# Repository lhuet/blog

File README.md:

Blog perso réalisé avec JBake -> http://lhuet.github.io/blog

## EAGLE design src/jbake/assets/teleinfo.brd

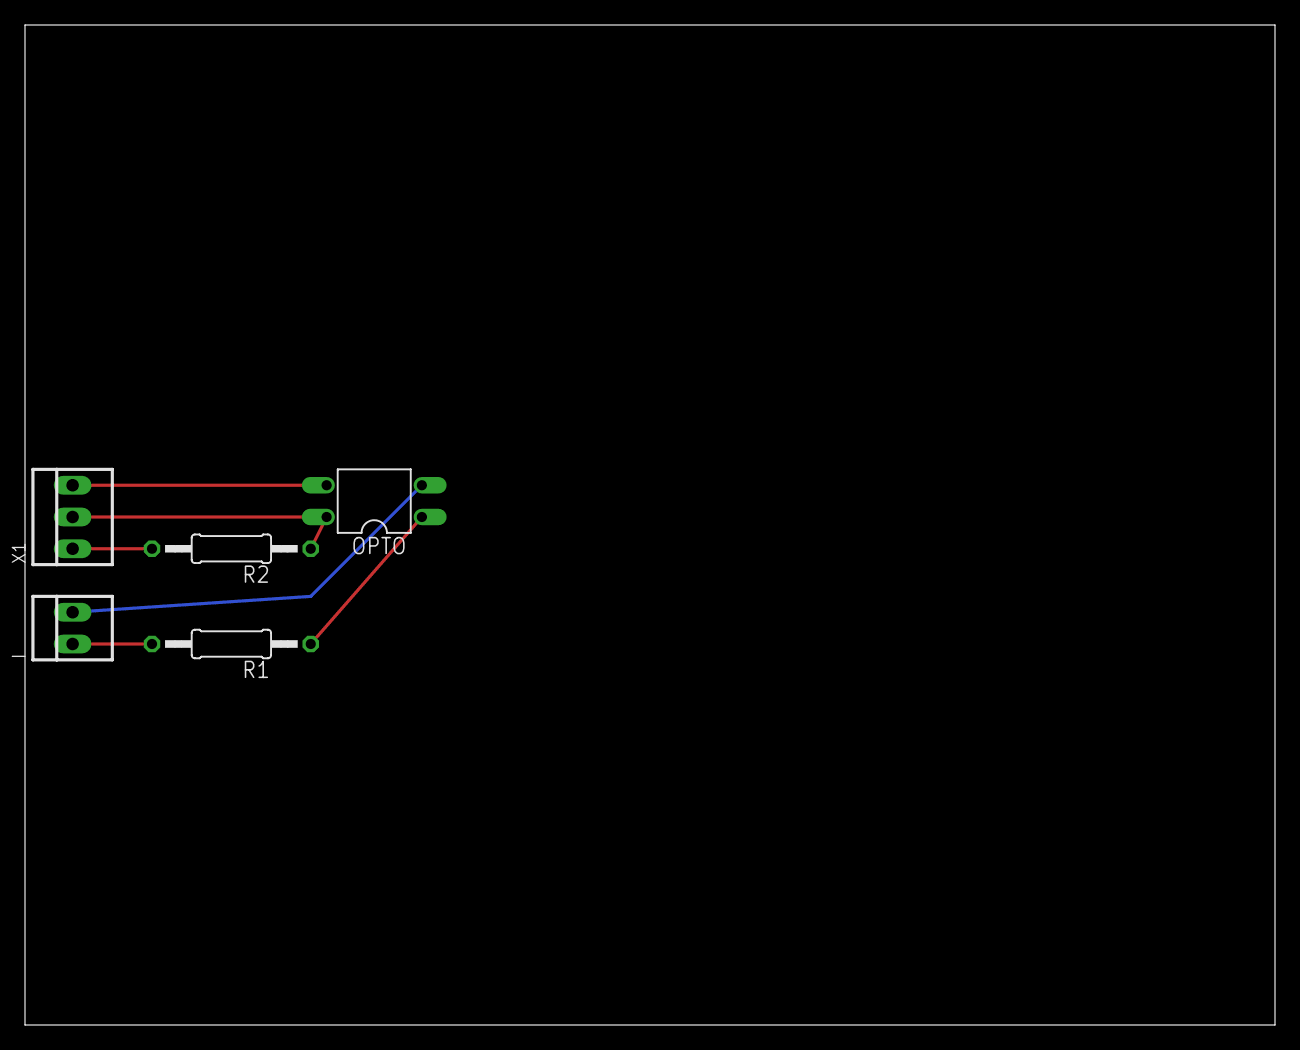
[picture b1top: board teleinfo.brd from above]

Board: 2 copper layers, 100.0 x 80.0 mm, 5 parts (0 on the bottom side), 6 nets.

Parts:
I: 22-23-2021
OPTO: SFH620A; DIL04
R1: 1.2k; 0207/12
R2: 3.3k; 0207/12
X1: 22-23-2031

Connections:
unnamed: OPTO.1, R1.1
unnamed: I.1, R1.2
unnamed: I.2, OPTO.2
unnamed: OPTO.4, R2.1, X1.2
unnamed: OPTO.3, X1.3
unnamed: R2.2, X1.1

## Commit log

2013-11-30 Premiere page de test
2013-12-01 init .gitignore
2013-12-01 init blog jbake
2013-12-01 ignore les fichiers générés
2013-12-01 migation template sous Bootstrap 3.0.2
2013-12-01 Template initial
2013-12-01 title change
2013-12-01 correction chemins css+js
2013-12-01 corrections chemin home
2013-12-01 déplacement des posts
2013-12-01 config host
2013-12-01 fix chemins + hostname feeds
2013-12-01 ajout themes bootstrap
2013-12-01 test theme
2013-12-01 test theme flatly
2013-12-01 changement favicon
2013-12-01 ajout theme yeti
2013-12-01 ajout facivon
2013-12-01 mise à jour page a propos
2013-12-01 ajout du titre
2013-12-01 ajout licence
2013-12-01 premier post
2013-12-01 changement de theme + maj version bootstrap en footer
2013-12-01 premier post et derniers ajustements
2013-12-01 fix adresse asciidoc
2013-12-01 maj titre menu
2013-12-01 maj style footer
2013-12-01 fix divers
2013-12-01 maj menu
2013-12-01 fix liens sur la page principale
2013-12-01 fix liens sur la page archive
2013-12-01 fix liens
2013-12-02 ajustements esthétiques
2013-12-02 maj article avant annonce ouverture blog
2013-12-02 ajout script Cedric Champeau
2013-12-02 ajustements premier post + styles
2013-12-02 ajout tracker google
2013-12-02 ajout feuille de style additionnelles
2013-12-03 fix lien licence
2013-12-08 post bbb overview
2013-12-08 ajout lien ubuntu sur bbb
2013-12-08 ajout commentaires disquss
2013-12-08 ajout boutons tweeter / gplus
2013-12-08 ajout post bbb overview
2013-12-08 fix lien image
2013-12-08 diminution taille titre h* par défaut
2013-12-14 fix titre flux RSS
2013-12-14 fix typo
2013-12-14 titre des pages dynamique (modif templates)
2013-12-14 version draft post jdk7/jdk8
2013-12-14 ajout URL blog dans Readme
2013-12-15 suppression jQuery et bootstrap.js
2013-12-15 ajout post jdk7/8 sur bbb
2013-12-15 ajout référence fichier ods
2013-12-15 ajout post jdk7 / 8 sur bbb
2013-12-15 modif conclusion post jdk7/8 bbb
2014-01-19 article montage teleinfo
2014-01-19 ignore gedit temp file
2014-01-19 projet eaglecad
2014-01-19 fix lien image compteur
2014-01-26 article préparation raspberry pi pour teleinfo
2014-06-02 Publish of github pages from Gradle
2014-06-02 jbake 2.3 migration + add build gradle
2014-06-06 fix link issues after jbake 2.3.0 migration
2014-06-06 fix rss feed link
2014-06-09 ajout post boitier de vote
2014-06-09 fix image
2014-06-09 (re)fix image
2014-06-09 fix typos
2014-06-10 rename likebox
2014-06-10 published likebox post
2014-06-10 fix title typo
2014-06-23 post gvm on beaglebone
2014-06-23 update gvm on beaglebone
2014-10-05 article rs485+arduino
2014-10-05 add archive link to menu
2014-10-05 add twitter & github links
2014-10-18 post getting started on Tessel
2014-10-18 fix typo digital/numerique
2015-05-20 add ESP8266 overview post
2015-05-28 add missing adoc files to master
2015-06-07 add draft post for k33g_org
2015-06-28 post 'cabler et flasher son ESP8266'
2015-06-28 suppression doublon
2015-10-04 add post ESP8266 / IDE Arduino
2015-10-04 rename post
2015-10-05 fix typo and fritzing schema
2016-11-02 add BuildWebappWithGradle prez
